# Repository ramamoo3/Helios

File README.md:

# Project Helios

Helios is a modular residential solar and LFP storage system for Tamil Nadu. Development is currently on one isolated battery port, scaled to a 12 V / 24 V laboratory fixture. The three-phase inverter and the production battery cabinet are later stages.

- [System architecture](HELIOS-ARCHITECTURE.md)
- [Build checklist](HELIOS-BUILD-CHECKLIST.md)
- [Whole-design software verification and fabrication status](HELIOS-VERIFICATION.md)
- [Open the KiCad bench project](circuits/battery-port/battery-port-bench.kicad_pro)
- [Bench component choices and current limits](circuits/battery-port/BENCH-PARTS.md)
- [Simulation and electrical checks](circuits/battery-port/README.md)

## Maintaining the project

GitHub `main` is the revision history. Before publishing, run the checks for the changed circuit or firmware and record the tool versions and known gaps. Keep KiCad caches and editor history local. Track independent engineering review and its findings against the revision under review. The verification tracker records fabrication status. [GitHub repository](https://github.com/ramamoo3/Helios) · [Verification tracker](HELIOS-VERIFICATION.md)

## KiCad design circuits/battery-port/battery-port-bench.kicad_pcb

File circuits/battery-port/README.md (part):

# Helios battery port · Rev A

One base-unit channel connects one protected 16S LFP cabinet to the shared DC link. Each cabinet gets its own converter and sensing electronics. The main low-voltage bench PCB includes split filled return planes, wider winding routes and mounting features. It passes KiCad geometry and schematic parity checks. Routed switching qualification, hardware cutoff integration and assembly fit remain open. The independent SPICE netlists use ideal supplies for the single-channel operating points and a finite capacitor for the two-channel link. [Bench PCB routing and verification](BENCH-PCB.md)

## Secondary-leg experiments

The rear-bypass DFN board is the current candidate for isolated-leg replay. Earlier experiments retain their original filenames so the recorded input hashes and reproduction commands remain usable. [Rear-bypass candidate](BENCH-SECONDARY-PROTECTED.md#routed-rear-driver-bypass)

| Archived layout studies | Evidence |
| --- | --- |
| TO-220, compact SON and integrated-driver coupons | [TO-220](BENCH-SECONDARY-LAYOUT.md) · [Compact SON](BENCH-SECONDARY-COMPACT.md) · [Driver coupon](BENCH-SECONDARY-DRIVEN.md) |
| Protected and isolated-driver coupons | [Protected layout](BENCH-SECONDARY-PROTECTED.md) · [Isolated-driver layout](BENCH-SECONDARY-PROTECTED.md#routed-isolated-driver-coupon) |
| Clamp, pin bypass and two DFN clamp layouts | [Local clamp](BENCH-SECONDARY-PROTECTED.md#local-high-side-clamp-revision) · [Pin bypass](BENCH-SECONDARY-PROTECTED.md#high-side-pin-bypass-revision) · [DFN layouts](BENCH-SECONDARY-PROTECTED.md#routed-dfn-clamp-and-pin-bias-screen) |

Open the [12 V / 24 V bench project](battery-port-bench.kicad_pro) and its [top-level schematic](battery-port-bench.kicad_sch) to inspect the wired assembly. The bench power sheet uses a 1:2 transformer and the series current detector. The separate 700 V power study remains outside this assembly. [Bench component selection, updated model and startup limits](BENCH-PARTS.md)

Open the [gate-feedback bench project](battery-port-bench-gate-feedback.kicad_pro) for the isolated cutoff bias, gate-voltage feedback and passive gate discharge revision. The [earlier protected project](battery-port-bench-protected.kicad_pro) reproduces the LTC7001 cold-start observations. Routing depends on component-level turn-off verification and independent interruption of a failed cutoff. [Gate-feedback verification](BENCH-LOCAL-SHUTDOWN.md#gate-feedback-and-passive-turn-off) · [Protected firmware and J701](BENCH-HRTIM.md#protected-bench-rail-sequence)

| Circuit | Editable source | Preview | Simulation |
| --- | --- | --- | --- |
| Isolated bidirectional power path | [Power schematic](battery-port-power.kicad_sch) | [View power sheet](battery-port-power.svg) | [Converter model](dab.lib), [operating points](dab-test.cir), [low-pack stress case](dab-low-pack.cir) |
| Battery voltage and signed current measurement | [Sensing schematic](battery-port-sense.kicad_sch) | [View sensing sheet](battery-port-sense.svg) | [Sensing model](sense.lib), [calibration test](sense-test.cir) |
| One bench half-bridge driver | [Driver schematic](battery-port-driver.kicad_sch) | [View driver](battery-port-driver.svg) | [Gate-load test](driver-test.cir) |
| Bench winding-current detector | [Detector schematic](battery-port-detector.kicad_sch) | [View detector](battery-port-detector.svg) | [Protection model](protection.lib) |
| Reset-dominant arm latch and logic | [Latch schematic](battery-port-triplogic.kicad_sch) | [View latch](battery-port-triplogic.svg) | [Fault sequences](protection-test.cir) |
| Cross-barrier enable and bias feedback | [Isolation schematic](battery-port-trip-isolation.kicad_sch) | [View isolation](battery-port-trip-isolation.svg) | [Two-domain permission test](protection-test.cir) |
| Local drive, logic and supervision (two instances) | [Bias sheet](battery-port-bias.kicad_sch) | [View bias](battery-port-bias.svg) | [Staggered startup and rail faults](bench-bias-test.cir) |
| Complementary PWM and secondary enable | [PWM sheet](battery-port-pwm.kicad_sch) | [View PWM](battery-port-pwm.svg) | [Dead time and local veto](bench-pwm-test.cir) |
| Bootstrap precharge and gate decode | [Precharge sheet](battery-port-precharge.kicad_sch) | [View decoder](battery-port-precharge.svg) | [Full converter precharge and bias-loss cases](vendor_startup_test.py) |
| Scaled power stage and external connections | [Power](battery-port-bench-power.kicad_sch) · [Terminals](battery-port-bench-io.kicad_sch) | [Power](battery-port-bench-power.svg) · [Terminals](battery-port-bench-io.svg) | [Scaled power model](dab-test.cir) |

## Measured in simulation

Positive link power means the battery supplies the base. Negative link power means the base supplies the charger side of the port. The nominal full-scale model uses a 51.2 V pack, a **provisional** 700 V link, a 1:14 transformer, 1.5 µH effective primary-referred transfer inductance, 180 µH magnetizing inductance and 50 kHz switching. D is the signed phase shift as a fraction of half a switching period. The 40–60 V sweep is a converter study range. The battery manufacturer and BMS set actual operating limits.

| Battery / link | D | Mean power into DC link | Observation |
| --- | ---: | ---: | --- |
| 12 V / 24 V scaled model | +0.20 / −0.20 | +23.0 / −23.1 W | Reversal at low voltage with 1:2 turns ratio and 10 µH transfer inductance |
| 51.2 V / 700 V | +0.20 / −0.20 | +2.730 / −2.730 kW | Battery supplies 53.8 A average on discharge and receives 52.9 A average on charge |
| 40 V / 700 V | +0.20 | +2.120 kW | Transfer-inductor current 58.9 A RMS |
| 60 V / 700 V | +0.20 | +3.211 kW | Transfer-inductor current 71.0 A RMS |
| 40 V / 700 V | +0.285 | +2.695 kW | Pack supplies 68.2 A average. Transfer inductor carries 79.0 A RMS and reaches 110.7 A peak |
| 50 V / 700 V matched winding voltages | 0 | −11.7 W | Residual draw at the link with both bridges switching. Disabled-port standby requires a separate test |

The standby deck measures both rails. With both bridges still switching at zero shift, the model draws 11.66 W from the DC link, returns 7.88 W to the pack and dissipates 3.78 W net. Disabling both bridges removes that circulation at the matched voltages and at the two voltage corners. The modeled off-state draw of 4–6 mW comes from assumed switch conductance. Actual standby depends on devices, the BMS, bias and housekeeping supplies, controls and inverter no-load consumption. [Standby simulation](dab-standby-test.cir)

The open-loop tests average 20 switching cycles. The ideal single-phase-shift comparison is `P = Vpack × (Vlink / turns_ratio) × D × (1 − |D|) / (2 × fs × Ltransfer)`. The tests check sign and magnitude against this expression. Device capacitance, diodes, winding resistance and switching transitions are simplified. Device losses, saturation, insulation performance, cooling and delivered household AC power require further work. [Phase-shift control reference](https://imperix.com/doc/implementation/dab-converter-control)

## Two cabinets on the same link

The scaled two-port test connects a 12 V pack and an 11 V pack through separate converters to one 24 V link with 2,200 µF capacitance. A constant 1.45 A load remains connected. Before the inhibit, the two channels supplied 0.957 A and 0.659 A into the link. At 2 ms the second port stopped receiving gate commands. In the final 0.4 ms the first port still supplied 0.957 A and the second contributed less than 1 µA in magnitude. The bus averaged 24.13 V before the inhibit and 23.74 V in the final window.

This demonstrates independent PWM inhibit in the scaled model. The disabled bridge retains diode paths. Fault isolation needs a separate disconnect. The observed voltage sag quantifies the need for a bus-voltage controller that redistributes load within the surviving pack's current limit. [Two-port SPICE deck](two-port-test.cir)

## Sensing circuit

The parent bench board uses a Kelvin-connected 0.5 mΩ primary rail shunt, R30, for INA240A1PW telemetry. Positive battery discharge raises the ADC signal above 1.65 V. The predicted transfer is 10 mV/A. The model produced 0.900, 1.650 and 2.400 V at −75, 0 and +75 A respectively. A 75 A continuous current alone dissipates 2.81 W in the shunt. Select the part using its temperature and pulse ratings. The isolated-leg test boards have a separate four-terminal 5 mΩ shunt for fast local shutdown at the low-side source. The standalone leg also labels that part R30. [INA240 datasheet](https://www.ti.com/lit/ds/symlink/ina240.pdf) · [5 mΩ shunt study](BENCH-SHUNT-TRANSFER.md)

The voltage divider uses three 56 kΩ resistors over 8.2 kΩ with 10 nF at its output. It produced 1.862, 2.383 and 2.792 V at 40, 51.2 and 60 V. Its nominal pole is 2.04 kHz. The shunt-amplifier model checks ideal DC gain and the external output filter. Input faults, amplifier dynamics, PWM rejection, ADC acquisition time, resistor tolerances and supply sequencing need characterization. The ADC and 3.3 V supply are local to each cabinet port. The controller interface requires isolated power and data where it crosses that boundary.

## Gate-driver bench circuit

Use one UCC27282DRC per leg, two legs per bridge. Each side of the transformer needs its own local bias supply and logic reference. The DRC package provides the enable input. Local pull-downs hold enable and gates low when undriven. Supply PWM with explicit dead time. [TI datasheet, pin table and application circuit](https://www.ti.com/lit/ds/symlink/ucc27282.pdf)

The 10 V bias, 4.7 Ω gate resistors and 100 nF nominal bootstrap capacitor are bench starting values. The vendor startup study also tested 60 nF and 120 nF at reduced bias. Select an exact capacitor MPN and use its minimum effective capacitance over DC bias, tolerance and temperature for the bootstrap refill and maximum on-time checks. The schematic shows the interface for local gate permission. The bench protection sheets provide the detector, latch and cross-barrier permission. The local bias and PWM sheets supply those interfaces in the bench hierarchy. [Bootstrap startup cases](BENCH-BOOTSTRAP.md)

The behavioral test checks high- and low-side gate-to-source voltage under valid commands, overlapping commands, overcurrent and loss of bias. It uses an imposed switch-node voltage, a 2 nF load and an illustrative 4 A fault threshold. Actual propagation, fault-current overshoot, bootstrap operation and physical gate turn-off time require bench measurement.

## Bench overcurrent shutdown

T2 senses the alternating primary winding current. On the bench variant, split the L1-to-T1 connection and insert T2 pins 4 and 3 in series. Wire its 1:100 secondary across the permanent 10 Ω burden, giving an ideal 100 mV/A about 1.65 V. U3, a TLV3202D, compares this signal with 1.246 V and 2.054 V. The **nominal ±4.04 A** threshold is a fixture design choice. Actual trip current depends on supply tolerance, CT droop, winding resistance, pulse shape, resistor tolerance, comparator offset and hysteresis. Check both polarities at 50 kHz. Sustained DC and same-leg shoot-through require independent rail current limiting and branch protection. [Coilcraft CT data and pin diagram](https://www.coilcraft.com/getmedia/12ba6199-a24d-486f-ba70-4b6bec000ed3/cst7030datasheet.pdf) · [TI TLV3202 comparator data and SOIC pin table](https://www.ti.com/lit/ds/symlink/tlv3202.pdf)

The comparator outputs feed an AND gate. Leaving the current window or losing either logic-domain power-good signal asserts the flip-flop's asynchronous clear. Arming samples the inverse of RUN on a rising ARM edge. A held ARM cannot restart the port after a trip. Two primary driver enables share PERMIT_P. Two secondary enables share PERMIT_S via the default-low ISO7710F. A second isolator returns SEC_OK to the primary latch. Each driver retains its own enable pull-down. [TI flip-flop](https://www.ti.com/lit/ds/symlink/sn74lvc1g74.pdf) · [TI quad AND](https://www.ti.com/lit/ds/symlink/sn74lvc08a.pdf) · [TI inverter](https://www.ti.com/lit/ds/symlink/sn74lvc1g04.pdf) · [TI isolator](https://www.ti.com/lit/ds/symlink/iso7710.pdf)

The test injects ±2.4 A ordinary excursions and separate +5.4 A and −5.4 A fault pulses. It checks both enable outputs, a held arm request across fault recovery, an arm attempt while running, deliberate re-arming and loss of secondary power-good. Both modeled comparator-input threshold crossings reached the remote enable midpoint in approximately 62 ns. This measures a behavioral delay assumption. The input current is injected, the digital rails stay powered and the model omits gate discharge, supply-collapse timing, core saturation and semiconductor fault current. For the physical fixture record current, comparator output, both enables and gate-to-source voltages together. Also test loss and restoration of each actual bias rail.

### Bench supplies, supervision and timing

Each bridge derives its rails from its own externally supplied DC port. P0 and S0 are separate. J3 is the 12 V primary port and J4 is the prebiased 24 V secondary port. This setup assumes that both rails are available before arming and that the receiving supply or an external load can absorb returned power. The 470 µF and 2,200 µF bulk capacitors each support a bridge with two dedicated 1 µF local ceramic bypass capacitors. Check bulk ripple, inrush and available voltage margin before assembly. [Bench part selections](BENCH-PARTS.md)

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
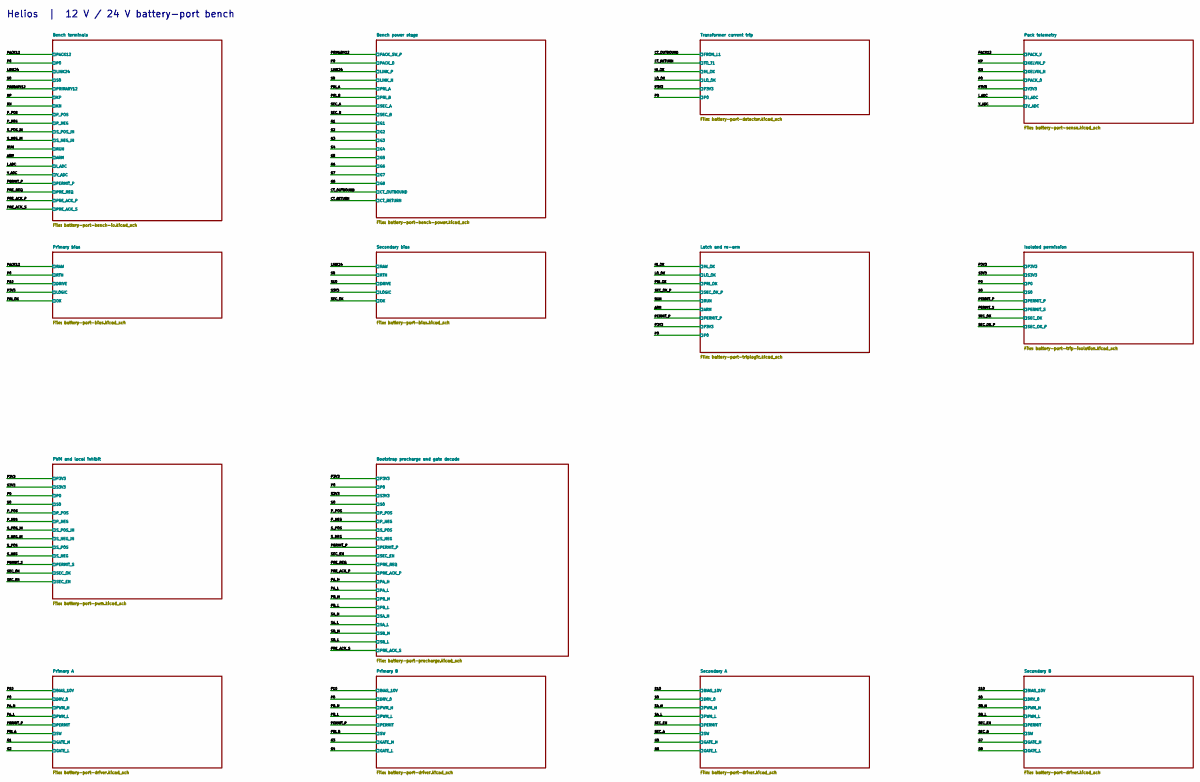
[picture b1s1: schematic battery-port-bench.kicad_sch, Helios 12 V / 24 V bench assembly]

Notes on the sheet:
Helios | 12 V / 24 V battery-port bench

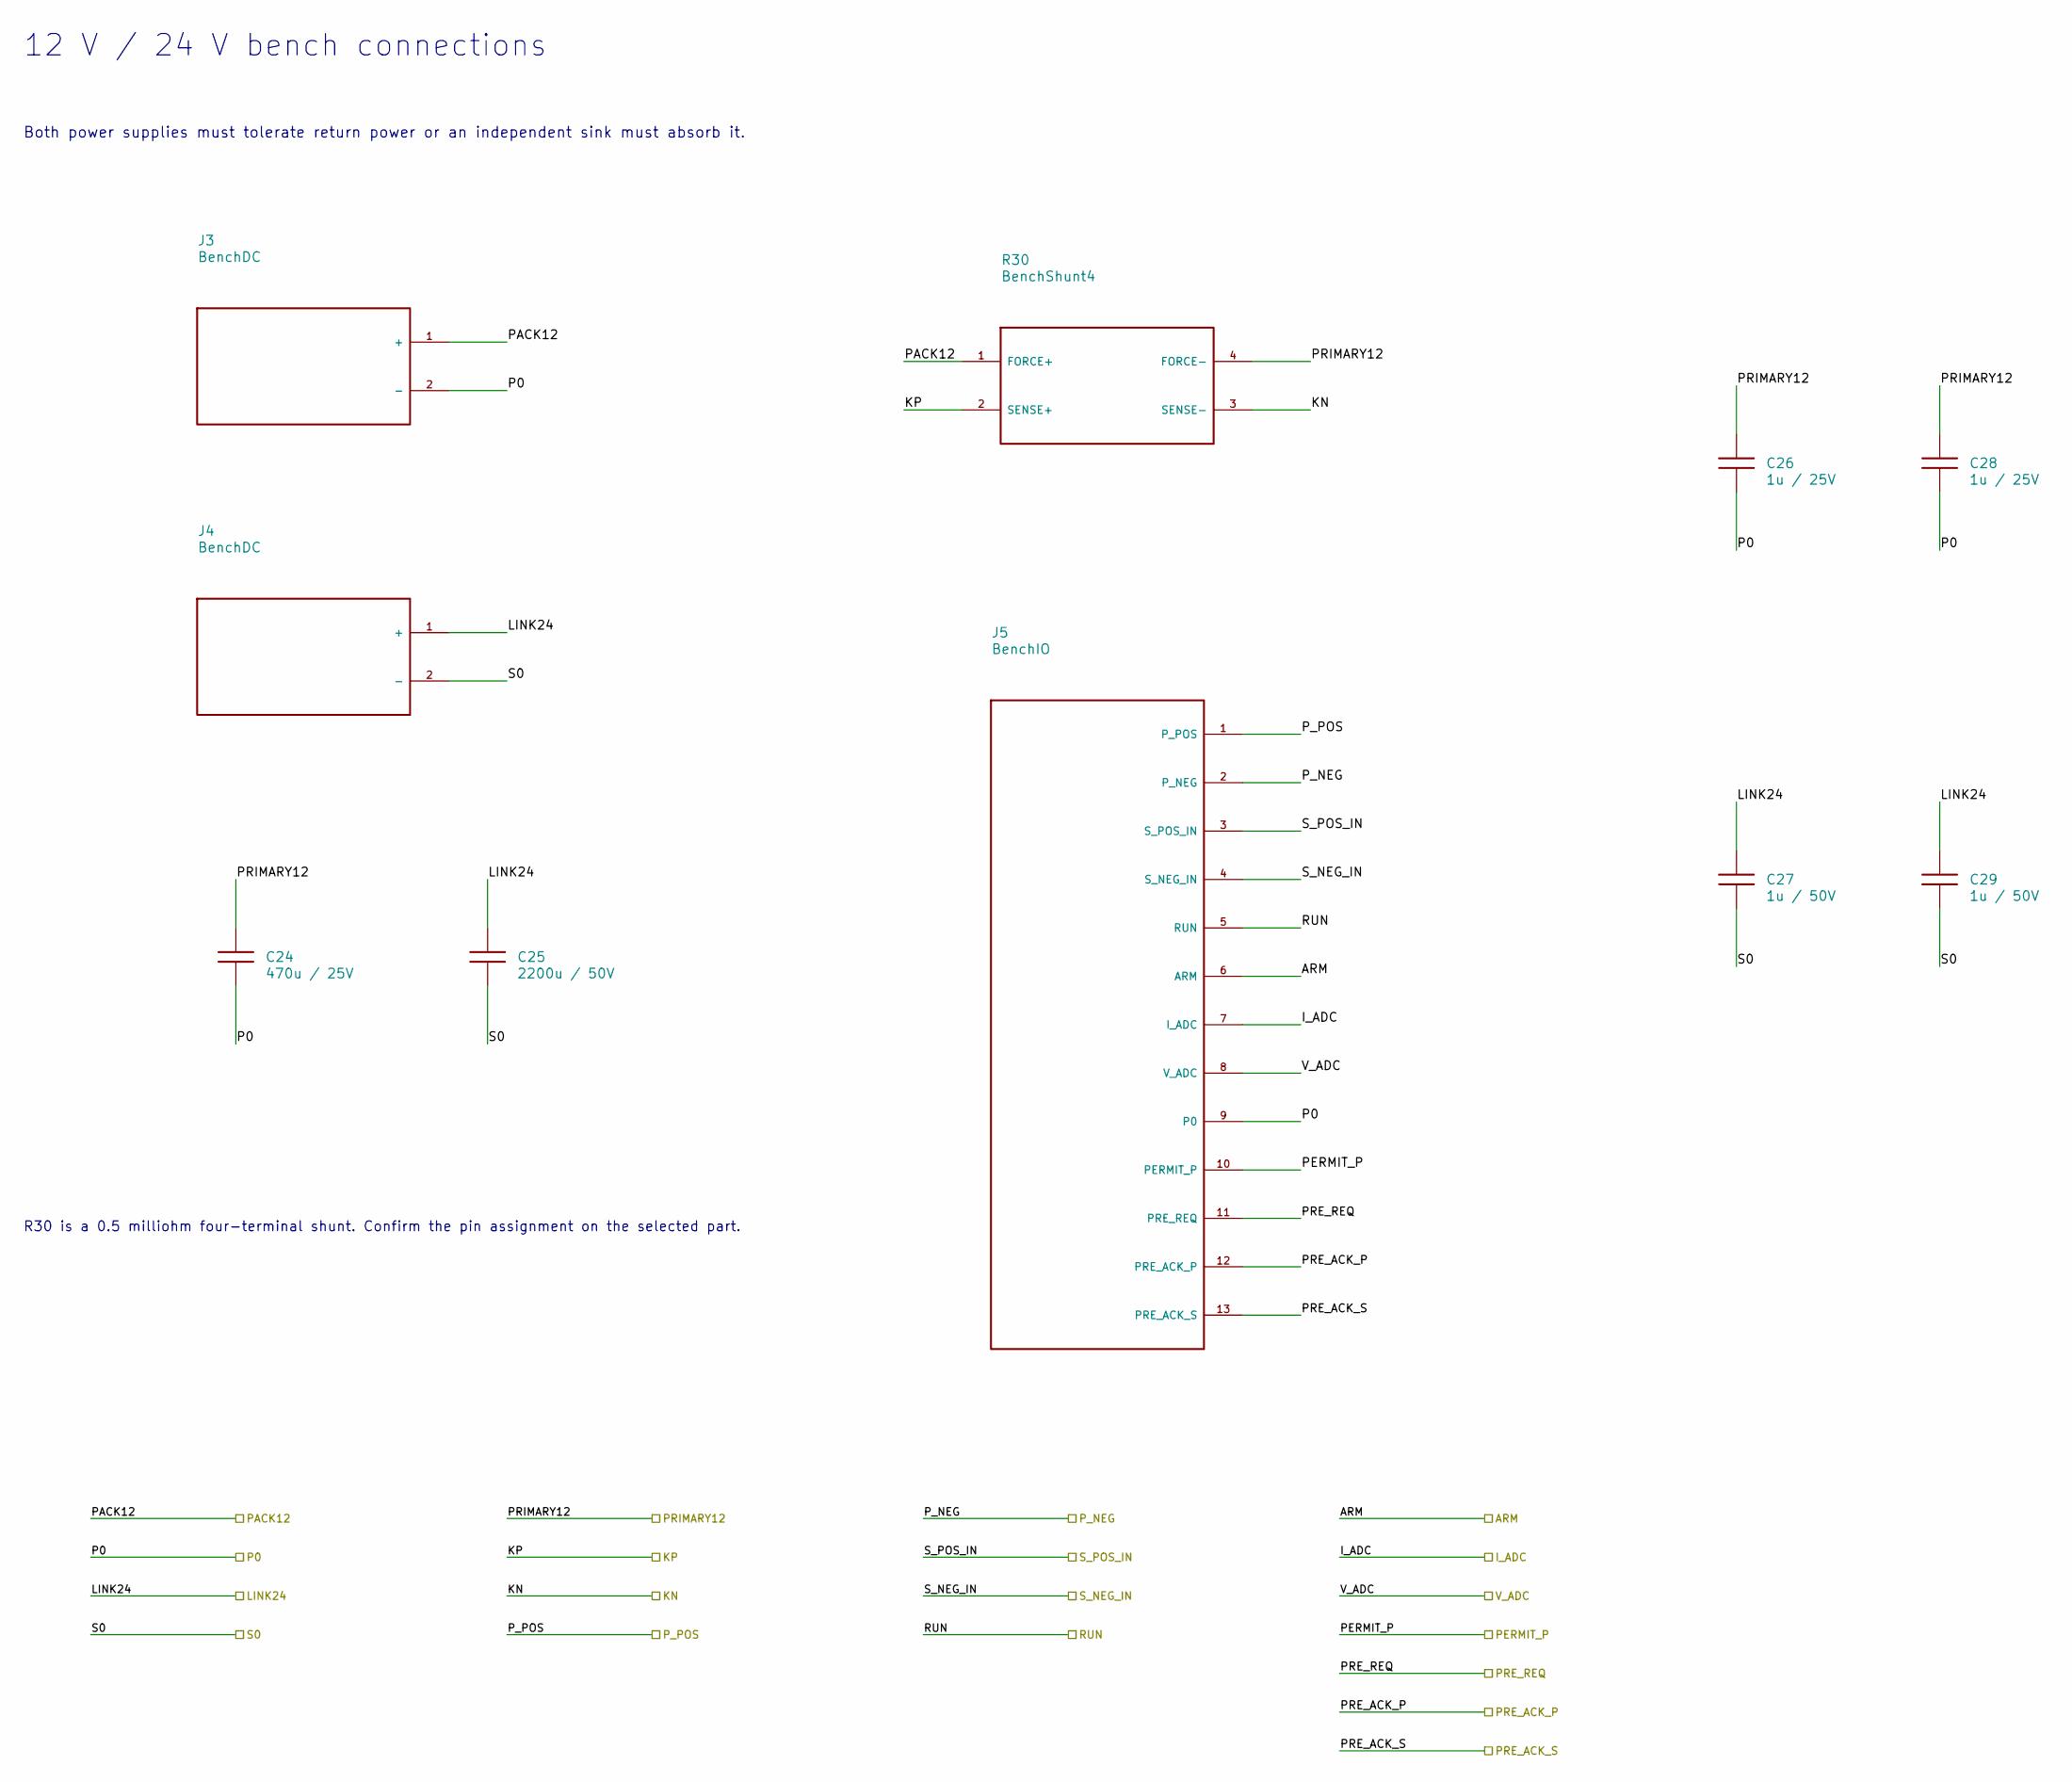
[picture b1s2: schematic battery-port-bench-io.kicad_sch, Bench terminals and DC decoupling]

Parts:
C24: 470u / 25V; CP_Radial_D10.0mm_P5.00mm
C25: 2200u / 50V; CP_Radial_D18.0mm_P7.50mm
C26, C28: 1u / 25V; C_0805_2012Metric
C27, C29: 1u / 50V; C_1206_3216Metric
J3, J4: BenchDC; TerminalBlock_Phoenix_MKDS-1,5-2-5.08_1x02_P5.08mm_Horizont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
J5: BenchIO; PinHeader_1x13_P2.54mm_Vertical
R30: BenchShunt4; Shunt_Bourns_CSS4J-4026

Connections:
/ARM: J5.6 (ARM); also elsewhere on the board
/I_ADC: J5.7 (I_ADC); also elsewhere on the board
/KN: R30.3 (SENSE-); also elsewhere on the board
/KP: R30.2 (SENSE+); also elsewhere on the board
/LINK24: C25.1, C27.1, C29.1, J4.1 (+); also elsewhere on the board
/P0: C24.2, C26.2, C28.2, J3.2 (-), J5.9 (P0); also elsewhere on the board
/PACK12: J3.1 (+), R30.1 (FORCE+); also elsewhere on the board
/PERMIT_P: J5.10 (PERMIT_P); also elsewhere on the board
/PRE_ACK_P: J5.12 (PRE_ACK_P); also elsewhere on the board
/PRE_ACK_S: J5.13 (PRE_ACK_S); also elsewhere on the board
/PRE_REQ: J5.11 (PRE_REQ); also elsewhere on the board
/PRIMARY12: C24.1, C26.1, C28.1, R30.4 (FORCE-); also elsewhere on the board
/P_NEG: J5.2 (P_NEG); also elsewhere on the board
/P_POS: J5.1 (P_POS); also elsewhere on the board
/RUN: J5.5 (RUN); also elsewhere on the board
/S0: C25.2, C27.2, C29.2, J4.2 (-); also elsewhere on the board
/S_NEG_IN: J5.4 (S_NEG_IN); also elsewhere on the board
/S_POS_IN: J5.3 (S_POS_IN); also elsewhere on the board
/V_ADC: J5.8 (V_ADC); also elsewhere on the board

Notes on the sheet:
12 V / 24 V bench connections
Both power supplies must tolerate return power or an independent sink must absorb it.
R30 is a 0.5 milliohm four-terminal shunt. Confirm the pin assignment on the selected part.

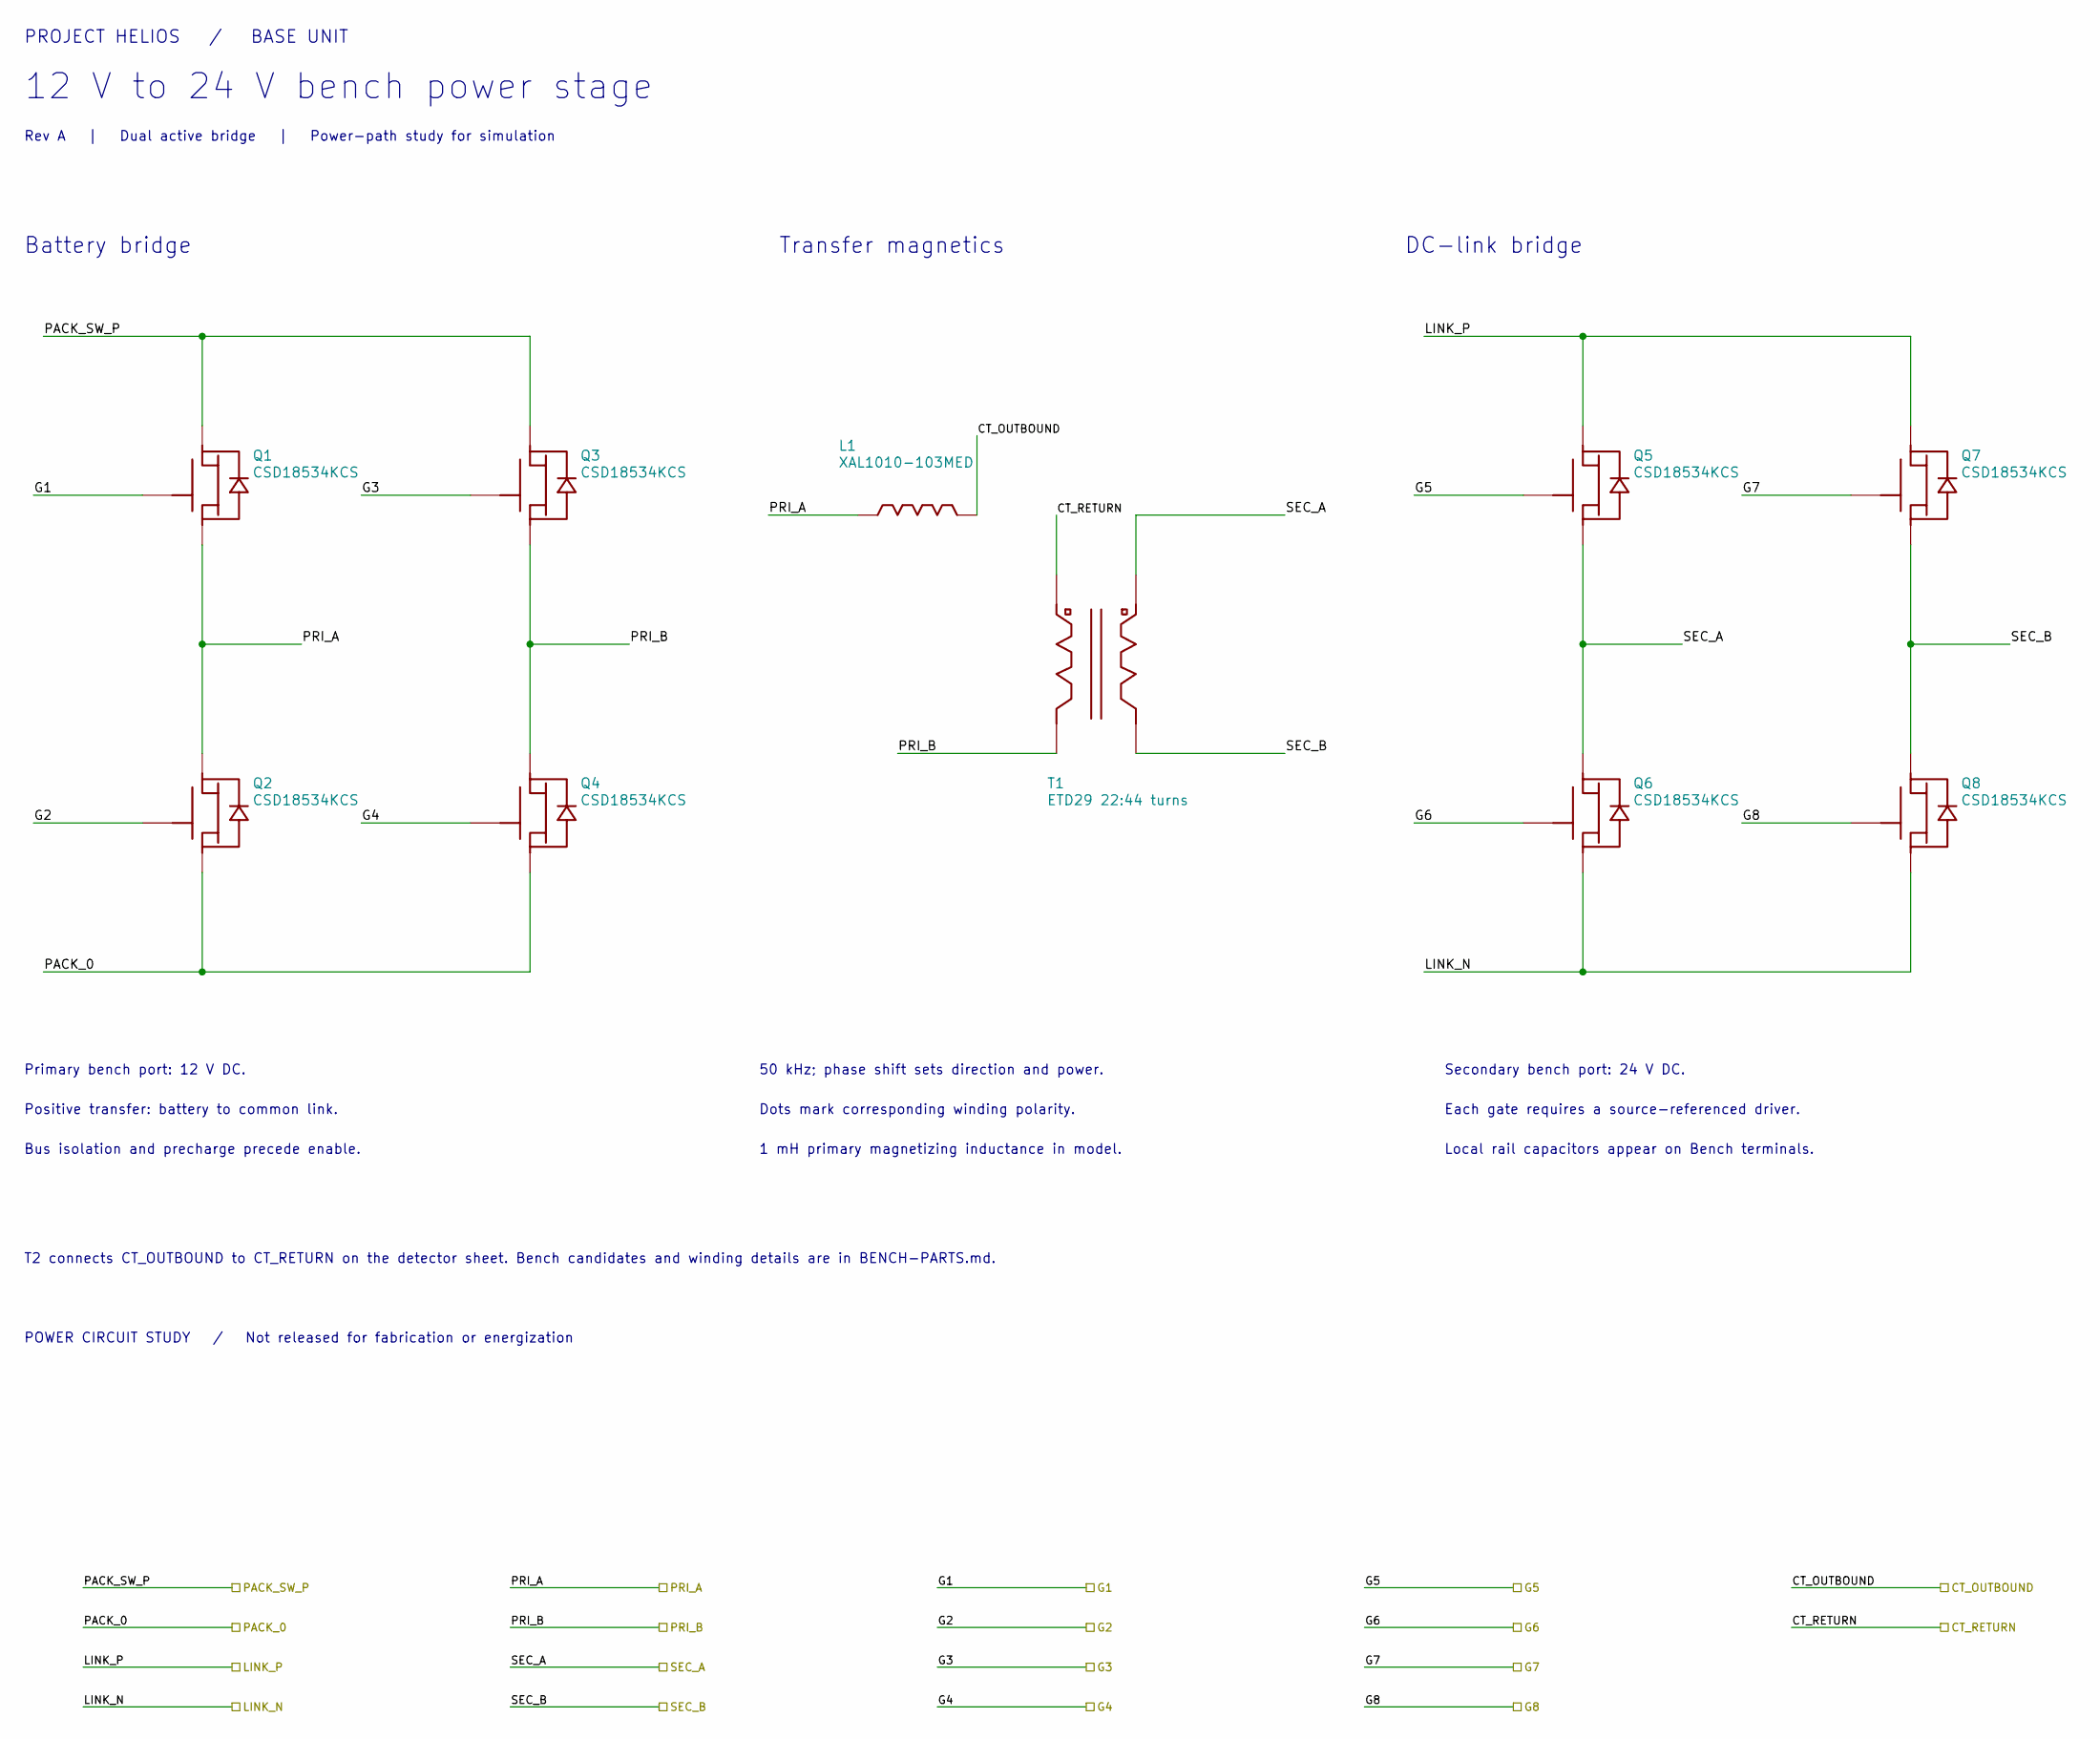
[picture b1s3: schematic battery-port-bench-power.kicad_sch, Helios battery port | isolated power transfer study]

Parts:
L1: XAL1010-103MED; L_Coilcraft_XAL1010-XXX
Q1, Q2, Q3, Q4, Q5, Q6, Q7, Q8: CSD18534KCS; TO-220-3_Vertical
T1: ETD29 22:44 turns; Transformer_TDK_B66359W1013T001_Helios

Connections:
/CT_OUTBOUND: L1.2; also elsewhere on the board
/CT_RETURN: T1.1; also elsewhere on the board
/G1: Q1.1 (G); also elsewhere on the board
/G2: Q2.1 (G); also elsewhere on the board
/G3: Q3.1 (G); also elsewhere on the board
/G4: Q4.1 (G); also elsewhere on the board
/G5: Q5.1 (G); also elsewhere on the board
/G6: Q6.1 (G); also elsewhere on the board
/G7: Q7.1 (G); also elsewhere on the board
/G8: Q8.1 (G); also elsewhere on the board
/LINK24: Q5.2 (D), Q7.2 (D); also elsewhere on the board
/P0: Q2.3 (S), Q4.3 (S); also elsewhere on the board
/PRIMARY12: Q1.2 (D), Q3.2 (D); also elsewhere on the board
/PRI_A: L1.1, Q1.3 (S), Q2.2 (D); also elsewhere on the board
/PRI_B: Q3.3 (S), Q4.2 (D), T1.2; also elsewhere on the board
/S0: Q6.3 (S), Q8.3 (S); also elsewhere on the board
/SEC_A: Q5.3 (S), Q6.2 (D), T1.3; also elsewhere on the board
/SEC_B: Q7.3 (S), Q8.2 (D), T1.4; also elsewhere on the board

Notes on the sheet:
PROJECT HELIOS / BASE UNIT
12 V to 24 V bench power stage
Rev A | Dual active bridge | Power-path study for simulation
Battery bridge
Transfer magnetics
DC-link bridge
Primary bench port: 12 V DC.
Positive transfer: battery to common link.
Bus isolation and precharge precede enable.
50 kHz; phase shift sets direction and power.
Dots mark corresponding winding polarity.
1 mH primary magnetizing inductance in model.
Secondary bench port: 24 V DC.
Each gate requires a source-referenced driver.
Local rail capacitors appear on Bench terminals.
T2 connects CT_OUTBOUND to CT_RETURN on the detector sheet. Bench candidates and winding details are in BENCH-PARTS.md.
POWER CIRCUIT STUDY / Not released for fabrication or energization

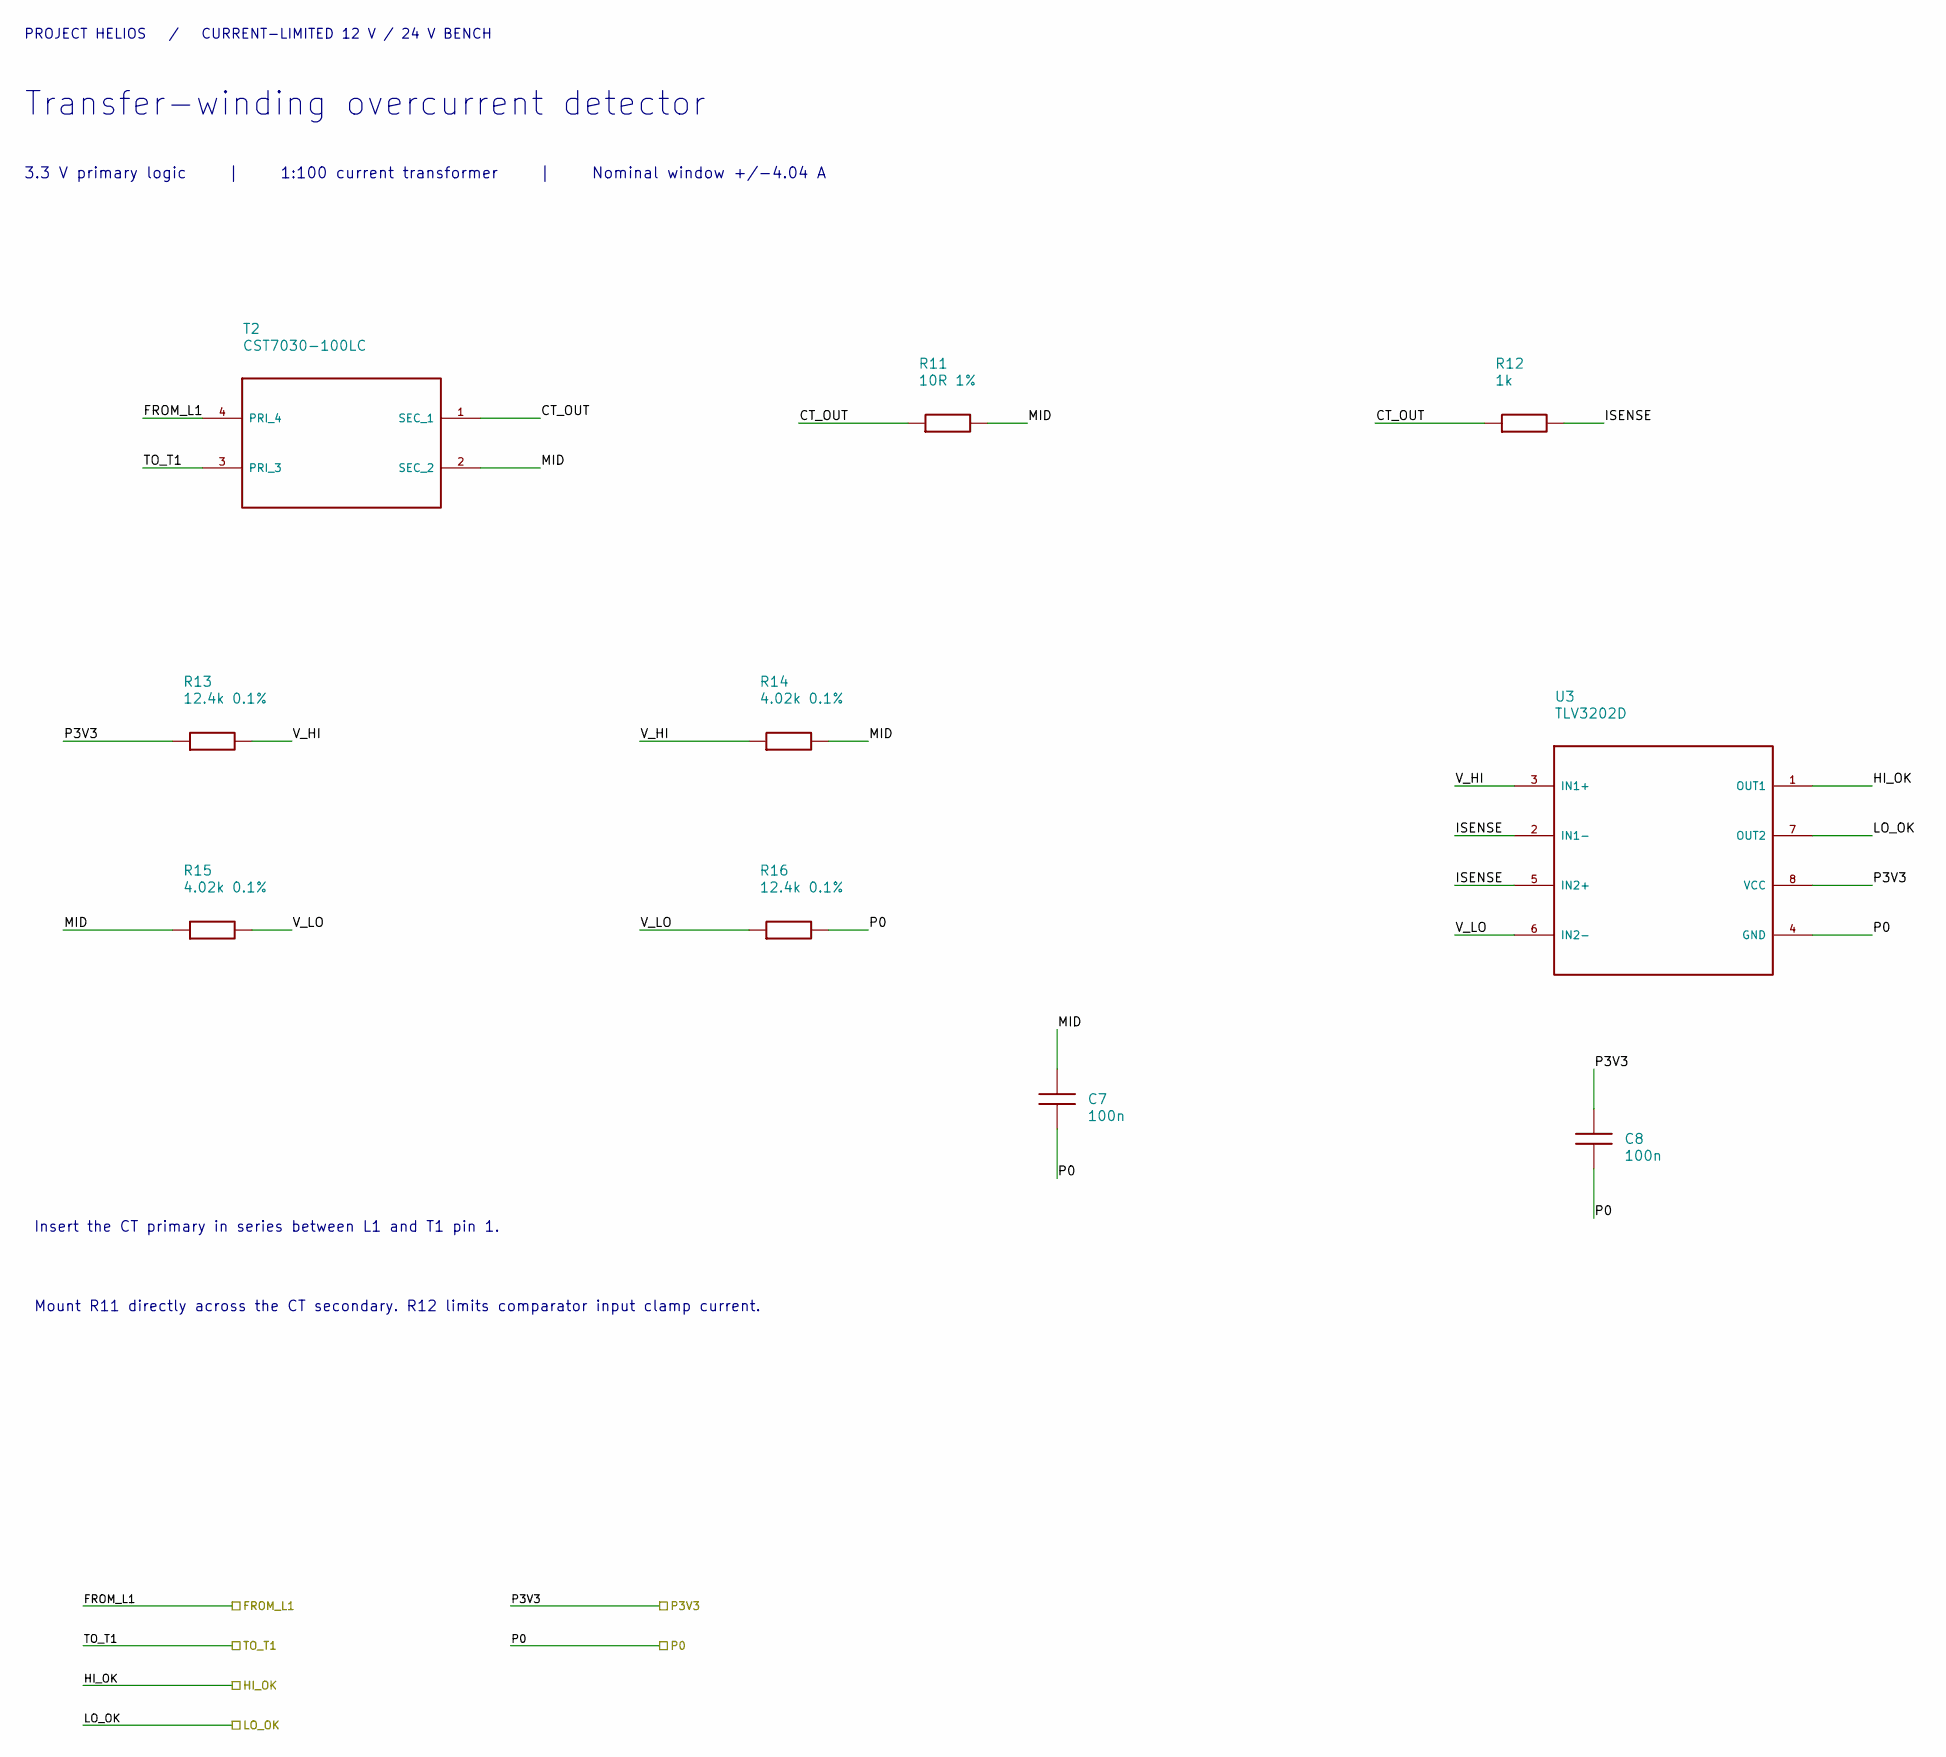
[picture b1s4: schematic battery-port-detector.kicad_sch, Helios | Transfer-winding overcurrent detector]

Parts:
C7, C8: 100n; C_0805_2012Metric; Voltage Rating 50 V; MPN CGA4J2X8R1H104K125AA
R11: 10R 1%; R_0805_2012Metric
R12: 1k; R_0805_2012Metric
R13, R16: 12.4k 0.1%; R_0805_2012Metric
R14, R15: 4.02k 0.1%; R_0805_2012Metric
T2: CST7030-100LC; Transformer_Coilcraft_CST7030
U3: TLV3202D; SOIC-8_3.9x4.9mm_P1.27mm

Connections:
/CT_OUTBOUND: T2.4 (PRI_4); also elsewhere on the board
/CT_RETURN: T2.3 (PRI_3); also elsewhere on the board
/HI_OK: U3.1 (OUT1); also elsewhere on the board
/LO_OK: U3.7 (OUT2); also elsewhere on the board
/P0: C7.2, C8.2, R16.2, U3.4 (GND); also elsewhere on the board
/P3V3: C8.1, R13.1, U3.8 (VCC); also elsewhere on the board
/Transformer current trip/CT_OUT: R11.1, R12.1, T2.1 (SEC_1)
/Transformer current trip/ISENSE: R12.2, U3.2 (IN1-), U3.5 (IN2+)
/Transformer current trip/MID: C7.1, R11.2, R14.2, R15.1, T2.2 (SEC_2)
/Transformer current trip/V_HI: R13.2, R14.1, U3.3 (IN1+)
/Transformer current trip/V_LO: R15.2, R16.1, U3.6 (IN2-)

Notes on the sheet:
PROJECT HELIOS / CURRENT-LIMITED 12 V / 24 V BENCH
Transfer-winding overcurrent detector
3.3 V primary logic | 1:100 current transformer | Nominal window +/-4.04 A
Insert the CT primary in series between L1 and T1 pin 1.
Mount R11 directly across the CT secondary. R12 limits comparator input clamp current.

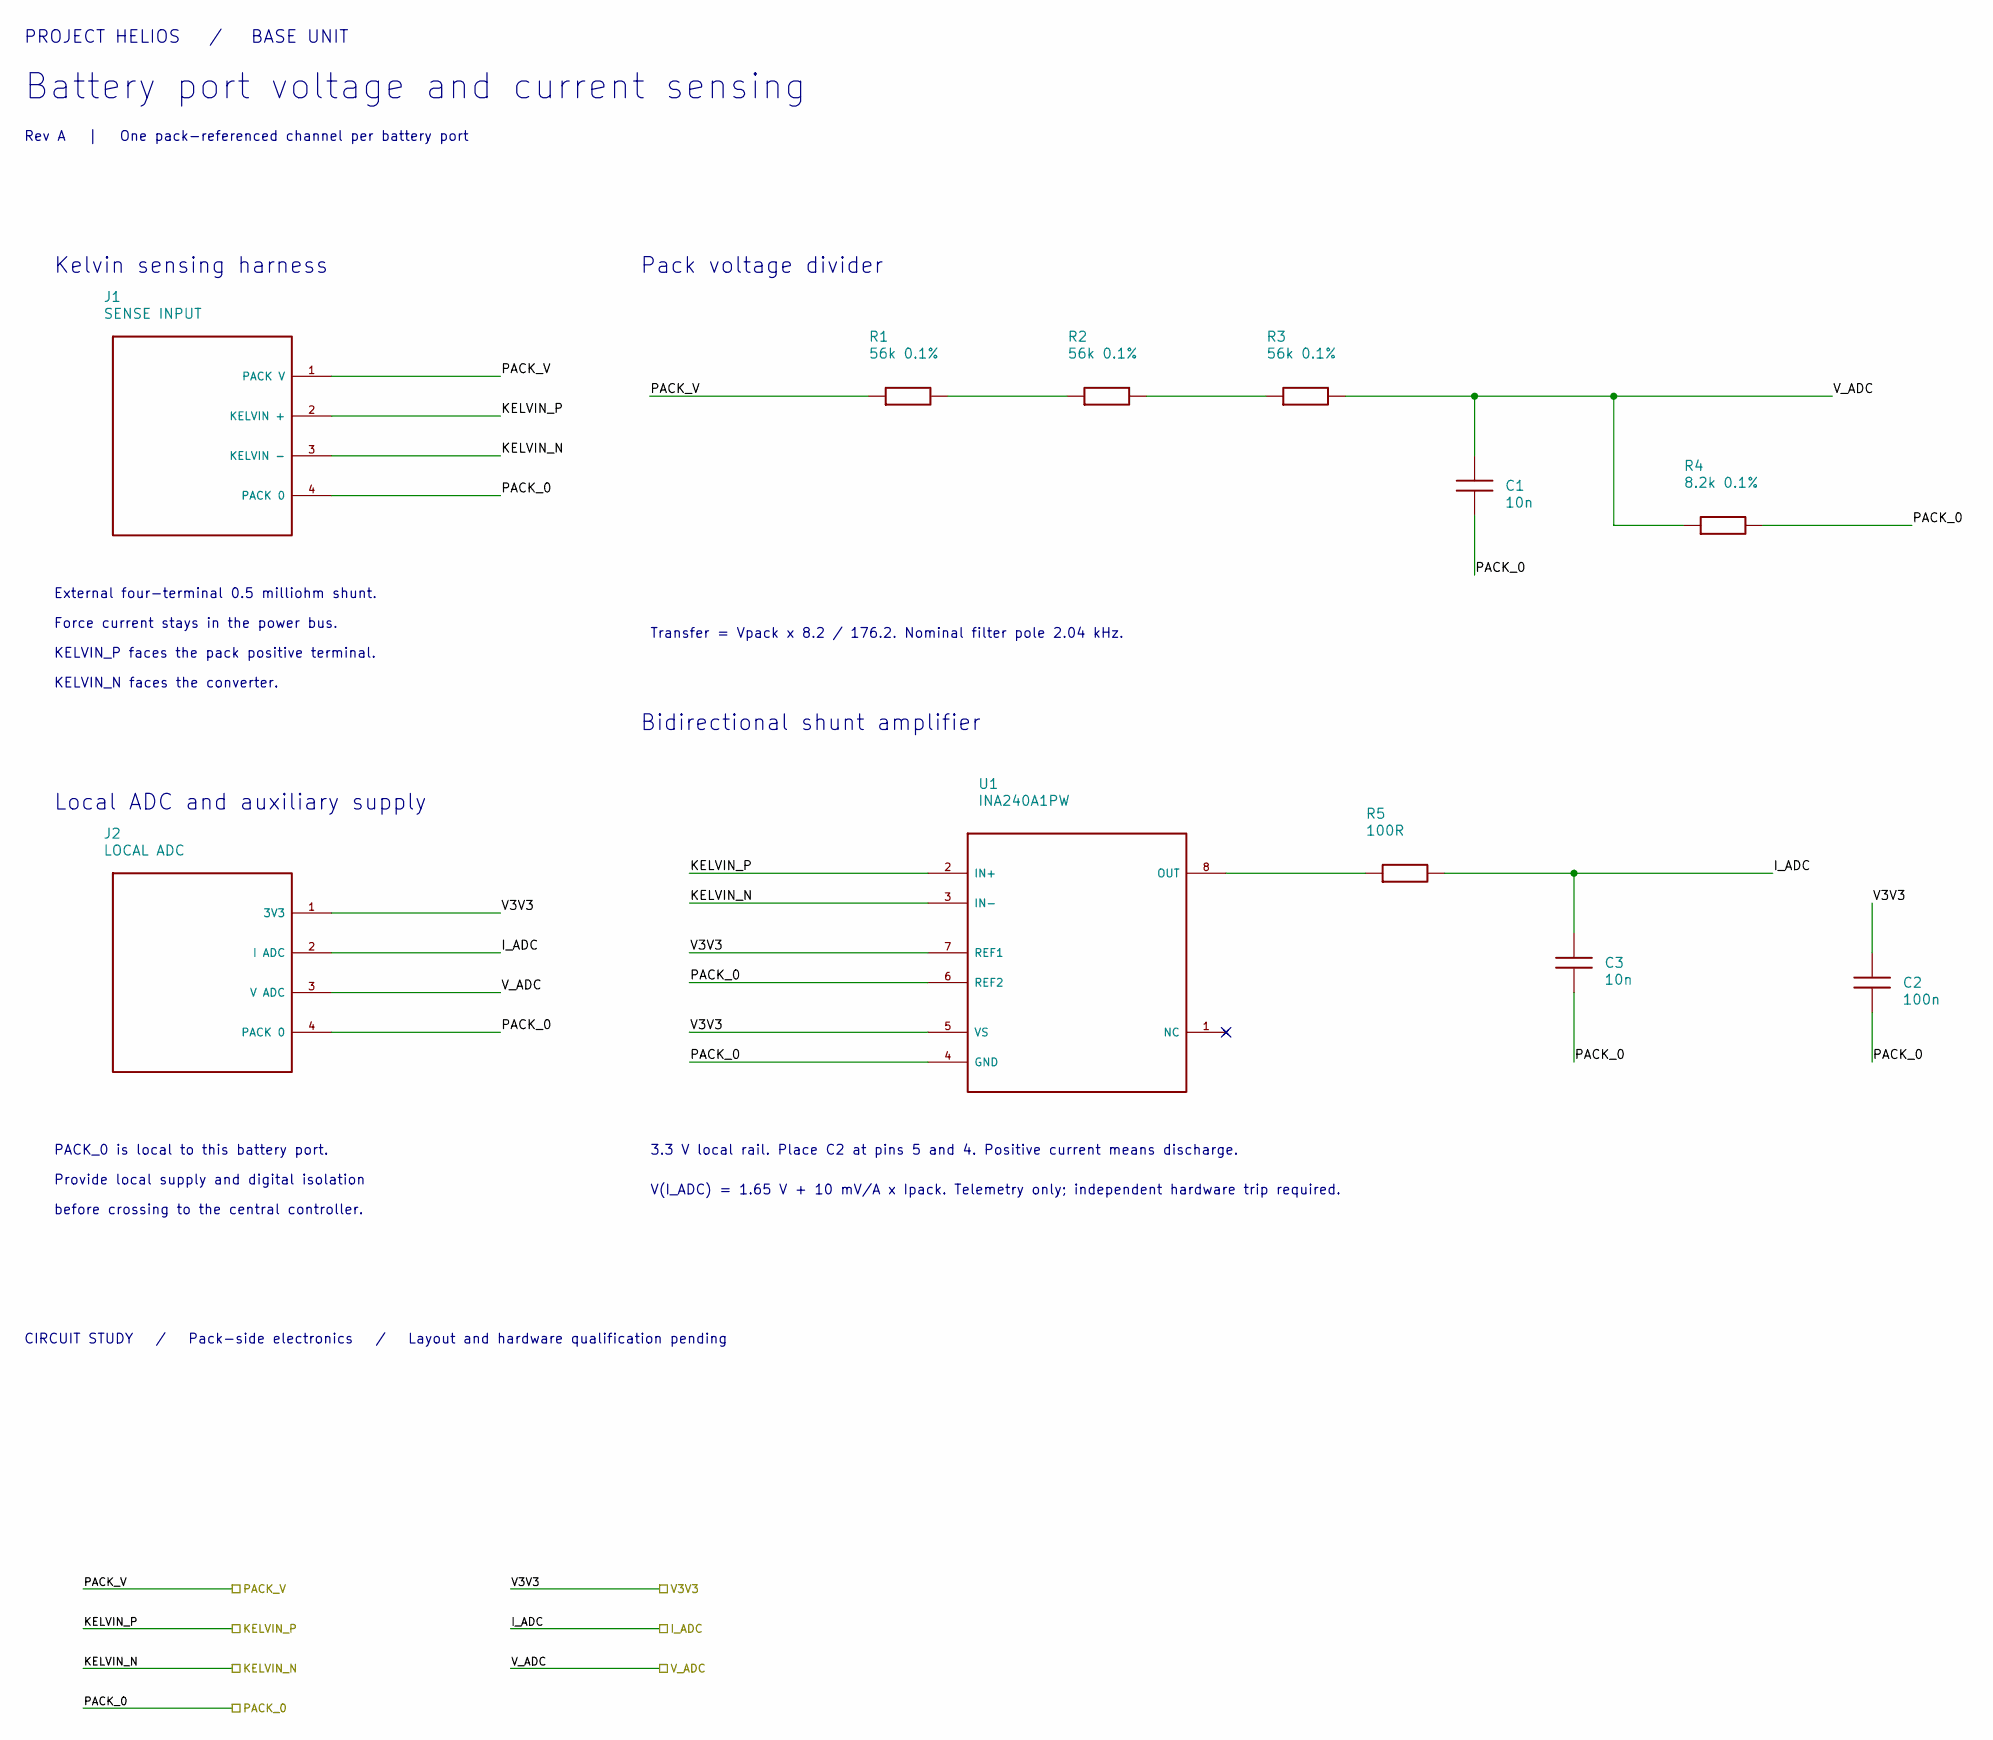
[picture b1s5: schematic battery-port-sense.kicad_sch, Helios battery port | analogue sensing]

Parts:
C1, C3: 10n; C_0805_2012Metric; Voltage Rating 50 V; MPN C2012C0G1H103J060AA
C2: 100n; C_0805_2012Metric; Voltage Rating 50 V; MPN CGA4J2X8R1H104K125AA
J1: SENSE INPUT; PinHeader_1x04_P2.54mm_Vertical
J2: LOCAL ADC; PinHeader_1x04_P2.54mm_Vertical
R1, R2, R3: 56k 0.1%; R_0805_2012Metric
R4: 8.2k 0.1%; R_0805_2012Metric
R5: 100R; R_0805_2012Metric
U1: INA240A1PW; TSSOP-8_4.4x3mm_P0.65mm

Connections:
/I_ADC: C3.1, J2.2 (I ADC), R5.2; also elsewhere on the board
/KN: J1.3 (KELVIN -), U1.3 (IN-); also elsewhere on the board
/KP: J1.2 (KELVIN +), U1.2 (IN+); also elsewhere on the board
/P0: C1.2, C2.2, C3.2, J1.4 (PACK 0), J2.4 (PACK 0), R4.2, U1.4 (GND), U1.6 (REF2); also elsewhere on the board
/P3V3: C2.1, J2.1 (3V3), U1.5 (VS), U1.7 (REF1); also elsewhere on the board
/PACK12: J1.1 (PACK V), R1.1; also elsewhere on the board
/V_ADC: C1.1, J2.3 (V ADC), R3.2, R4.1; also elsewhere on the board
unnamed: R1.2, R2.1
unnamed: R2.2, R3.1
unnamed: R5.1, U1.8 (OUT)

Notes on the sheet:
PROJECT HELIOS / BASE UNIT
Battery port voltage and current sensing
Rev A | One pack-referenced channel per battery port
Kelvin sensing harness
External four-terminal 0.5 milliohm shunt.
Force current stays in the power bus.
KELVIN_P faces the pack positive terminal.
KELVIN_N faces the converter.
Local ADC and auxiliary supply
PACK_0 is local to this battery port.
Provide local supply and digital isolation
before crossing to the central controller.
Pack voltage divider
Transfer = Vpack x 8.2 / 176.2. Nominal filter pole 2.04 kHz.
Bidirectional shunt amplifier
3.3 V local rail. Place C2 at pins 5 and 4. Positive current means discharge.
V(I_ADC) = 1.65 V + 10 mV/A x Ipack. Telemetry only; independent hardware trip required.
CIRCUIT STUDY / Pack-side electronics / Layout and hardware qualification pending
